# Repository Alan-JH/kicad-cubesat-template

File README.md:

# kicad-cubesat-template
 Template for PC104 cubesat stack layout
 
 Designed in KiCAD v6.0.2

# Installation

 Open KiCad, select 'Preferences' -> 'Configure Paths'

 Find the entry named 'KICAD_USER_TEMPLATE_DIR', or add it if it doesn't exist

 Either record the directory or set it to a directory you will not change

 Copy the 'PC104 Cubesat Template' folder into that directory

 Restart KiCad

 To use the template, select 'New Project From Template' -> 'User Templates'

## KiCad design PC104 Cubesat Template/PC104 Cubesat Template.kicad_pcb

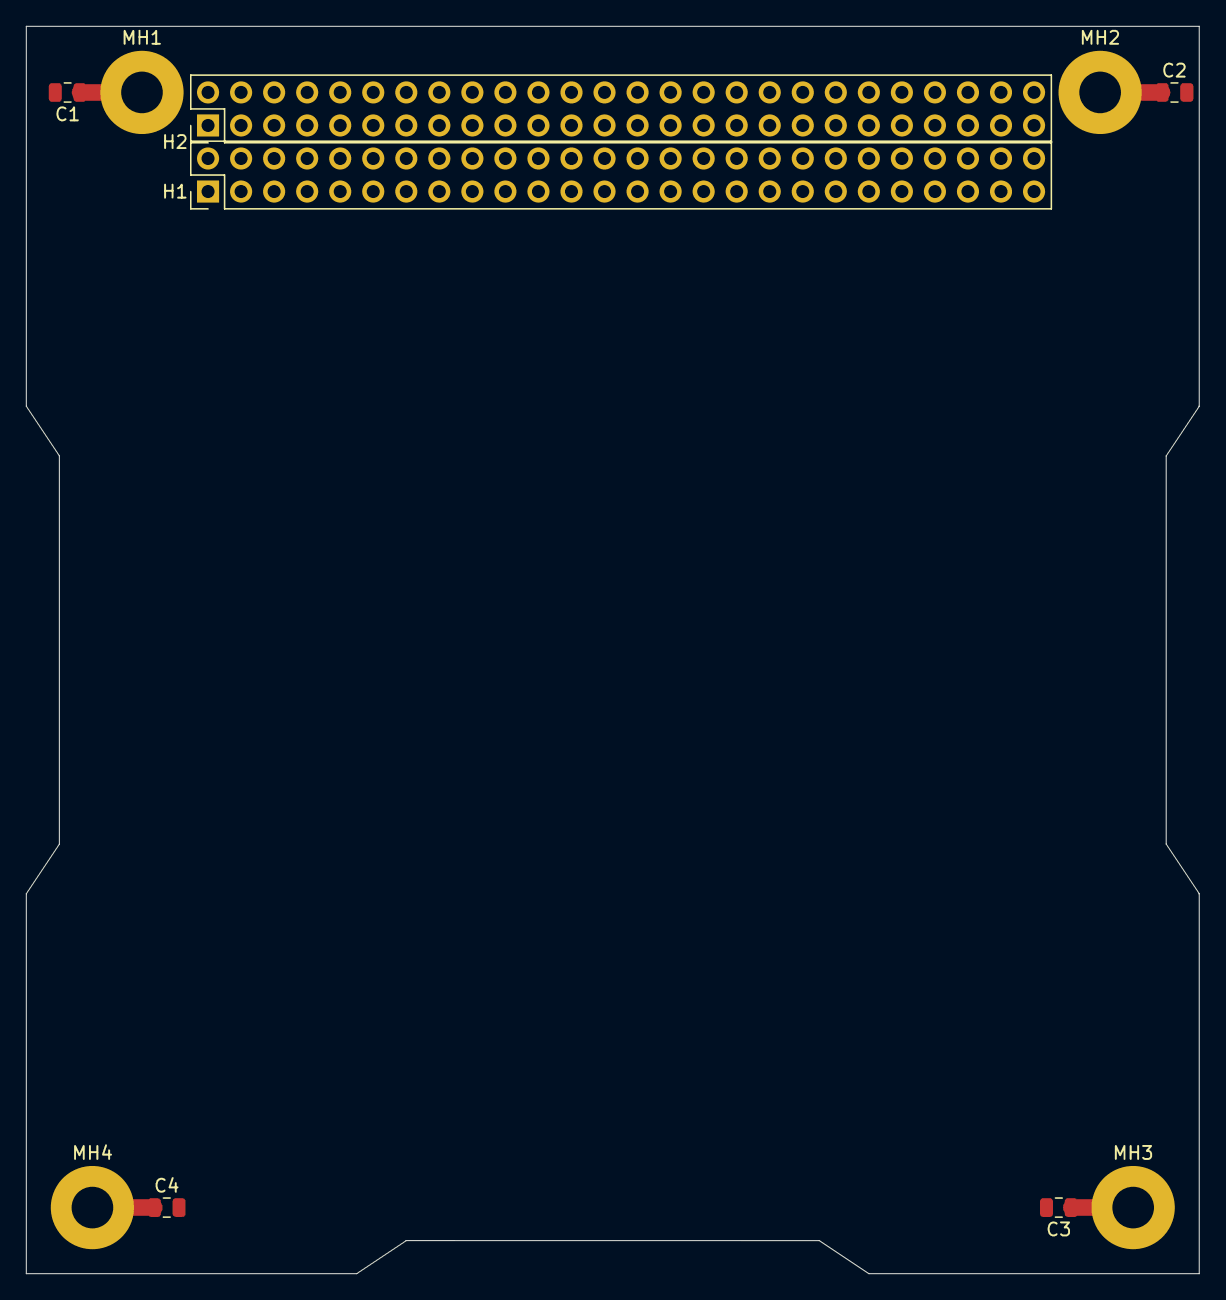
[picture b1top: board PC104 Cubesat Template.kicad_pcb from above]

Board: 2 copper layers, 90.2 x 95.9 mm, 10 parts (0 on the bottom side), 8 nets.

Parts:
C1, C2, C3, C4: 0.1uF; C_0805_2012Metric
H1, H2: Stack Header; PinHeader_2x26_P2.54mm_Vertical
MH1, MH2, MH3, MH4: M3; MountingHole_3.2mm_M3_Pad

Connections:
+3V3: H2.27, H2.28
+5V: H2.25, H2.26
+BATT: H2.45, H2.46
GND: C1.2, C2.2, C3.2, C4.2, H2.29, H2.30, H2.32
unnamed: C1.1, MH1.1
unnamed: C2.1, MH2.1
unnamed: C3.1, MH3.1
unnamed: C4.1, MH4.1

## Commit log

2022-03-04 Template
2022-03-04 Version info
2022-03-04 add images
2022-03-04 Add info.html
2022-03-04 update gitignore
2022-03-04 remove dir
2022-03-04 remove step
2022-03-04 test gitignore
2022-03-04 remove test
2022-03-04 Fix gitignore
2022-03-04 resize image
2022-03-04 add installation instructions
2022-03-25 add tj bus specific pins
